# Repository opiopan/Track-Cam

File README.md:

trackCAM
---

trackCAM is a shield board for Raspberry Pi to realize 2 axis tracking camera controll capability and RC TX collaboration capability.

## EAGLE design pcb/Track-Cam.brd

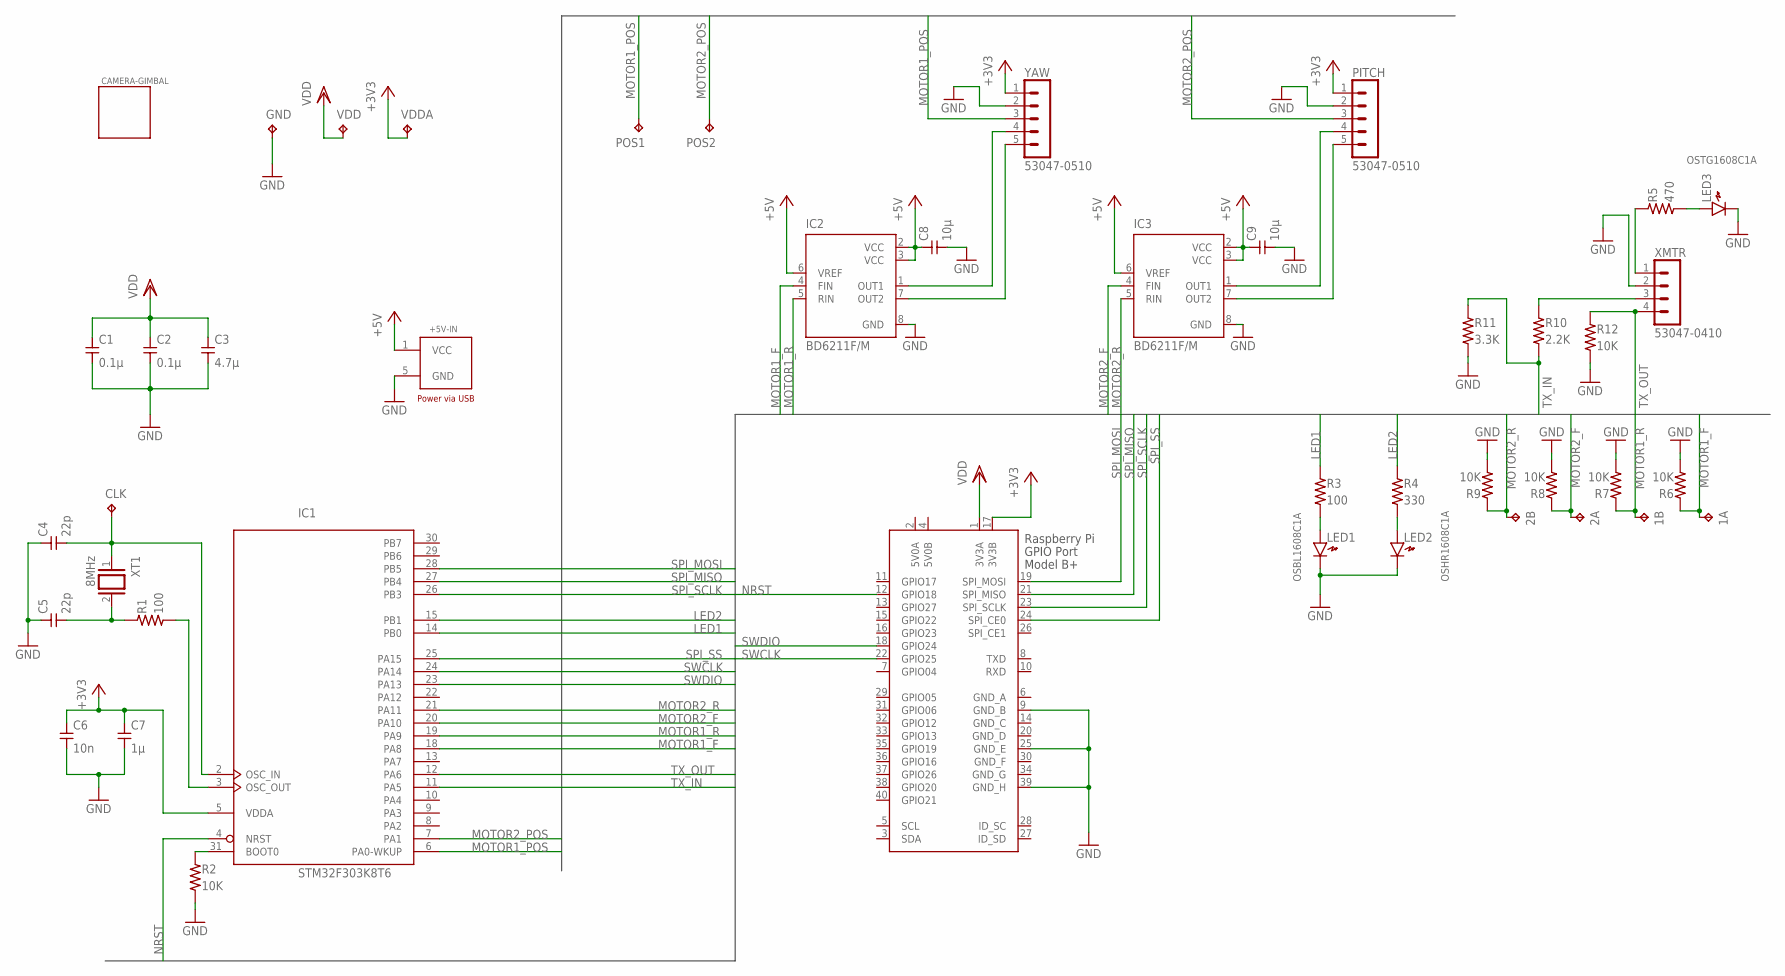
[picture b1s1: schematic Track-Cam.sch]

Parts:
1A, 1B, 2A, 2B: TPB1,27; B1,27
+5V-IN: MRUSB-2B-D14NI-S306/M; MICRO-USB-POWER/M
C1, C2: 0.1μ; SMD2012
C3: 4.7μ; SMD2012
C4, C5: 22p; SMD1608
C6: 10n; SMD2012
C7: 1μ; SMD2012
C8, C9: 10μ; SMD2012
CAMERA-GIMBAL: SG-90-CAMERA-MOUNT/NR; SG90-CAMERA-MOUNT-NR
CLK: TPB1,27; B1,27
GND: TPB1,27; B1,27
IC1: STM32F303K8T6; LQFP32-M
IC2, IC3: BD6211F/M; SOP8/M
LED1, LED2, LED3: LED1608
P1: RASPI_BOARD_B+#_HC; RASPI_BOARD_B+HAT_CF
PITCH: 53047-0510
POS1, POS2: TPB1,27; B1,27
R1, R3: 100; SMD2012
R2, R6, R7, R8, R9, R12: 10K; SMD2012
R4: 330; SMD2012
R5: 470; SMD2012
R10: 2.2K; SMD2012
R11: 3.3K; SMD2012
VDD: TPB1,27; B1,27
VDDA: TPB1,27; B1,27
XMTR: 53047-0410
XT1: 8MHz; QS
YAW: 53047-0510

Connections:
5V0A: P1.2 (5V0A)
5V0B: P1.4 (5V0B)
+3V3: C6.1, C7.1, IC1.5 (VDDA), P1.17 (3V3B), PITCH.1, VDDA.TP, YAW.1
+5V: +5V-IN.1 (VCC), C8.1, C9.1, IC2.2 (VCC), IC2.3 (VCC), IC2.6 (VREF), IC3.2 (VCC), IC3.3 (VCC), IC3.6 (VREF)
BOOT0: IC1.31 (BOOT0), R2.1
GND: +5V-IN.5 (GND), C1.2, C2.2, C3.2, C4.1, C5.1, C6.2, C7.2, C8.2, C9.2, GND.TP, IC1.16 (GND), IC1.32 (GND), IC2.8 (GND), IC3.8 (GND), LED1.K, LED2.K, LED3.K, P1.9 (GND_B), P1.25 (GND_E), P1.39 (GND_H), PITCH.2, R2.2, R6.2, R7.2, R8.2, R9.2, R11.2, R12.2, XMTR.2, YAW.2
GND_A: P1.6 (GND_A)
GND_C: P1.14 (GND_C)
GND_D: P1.20 (GND_D)
GND_F: P1.30 (GND_F)
GND_G: P1.34 (GND_G)
LED1: IC1.14 (PB0), R3.1
LED2: IC1.15 (PB1), R4.1
MOTOR1+: IC2.1 (OUT1), YAW.4
MOTOR1-: IC2.7 (OUT2), YAW.5
MOTOR1_F: 1A.TP, IC1.18 (PA8), IC2.4 (FIN), R6.1
MOTOR1_POS: IC1.6 (PA0-WKUP), POS1.TP, YAW.3
MOTOR1_R: 1B.TP, IC1.19 (PA9), IC2.5 (RIN), R7.1
MOTOR2+: IC3.1 (OUT1), PITCH.4
MOTOR2-: IC3.7 (OUT2), PITCH.5
MOTOR2_F: 2A.TP, IC1.20 (PA10), IC3.4 (FIN), R8.1
MOTOR2_POS: IC1.7 (PA1), PITCH.3, POS2.TP
MOTOR2_R: 2B.TP, IC1.21 (PA11), IC3.5 (RIN), R9.1
unnamed: C5.2, R1.1, XT1.2
unnamed: LED1.A, R3.2
unnamed: LED2.A, R4.2
unnamed: R5.1, XMTR.1
unnamed: LED3.A, R5.2
NRST: IC1.4 (NRST), P1.12 (GPIO18)
OSC_IN: C4.2, CLK.TP, IC1.2 (OSC_IN), XT1.1
OSC_OUT: IC1.3 (OSC_OUT), R1.2
SPI_MISO: IC1.27 (PB4), P1.21 (SPI_MISO)
SPI_MOSI: IC1.28 (PB5), P1.19 (SPI_MOSI)
SPI_SCLK: IC1.26 (PB3), P1.23 (SPI_SCLK)
SPI_SS: IC1.25 (PA15), P1.24 (SPI_CE0)
SWCLK: IC1.24 (PA14), P1.22 (GPIO25)
SWDIO: IC1.23 (PA13), P1.18 (GPIO24)
TX_IN: IC1.11 (PA5), R10.2, R11.1
TX_IN_5V: R10.1, XMTR.3
TX_OUT: IC1.12 (PA6), R12.1, XMTR.4
VDD: C1.1, C2.1, C3.1, IC1.1 (VDD), IC1.17 (VDD), P1.1 (3V3A), VDD.TP

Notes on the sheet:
OSBL1608C1A
OSHR1608C1A
OSTG1608C1A

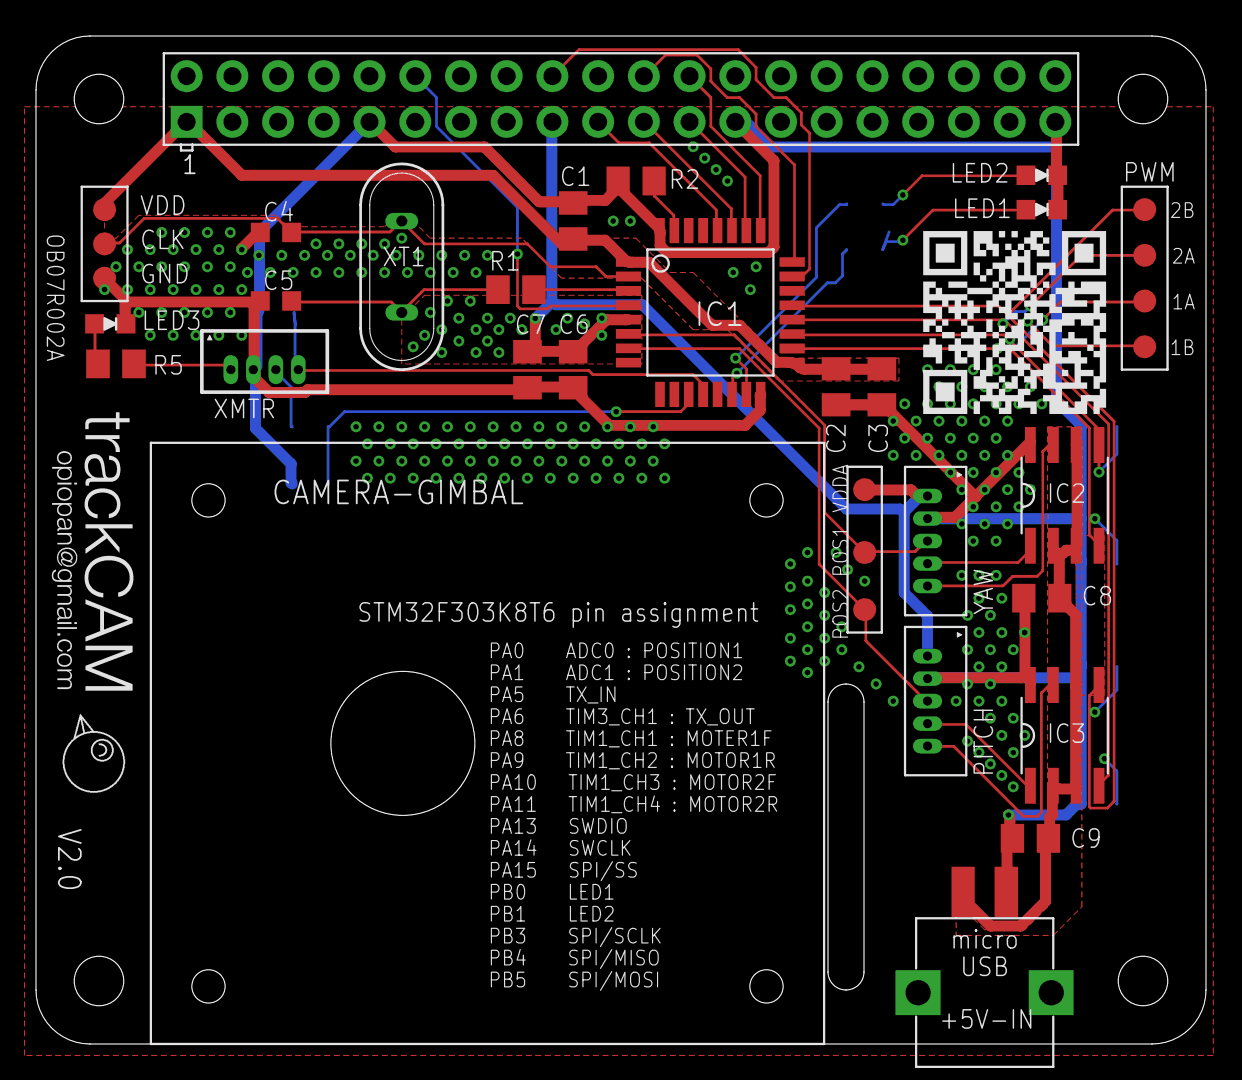
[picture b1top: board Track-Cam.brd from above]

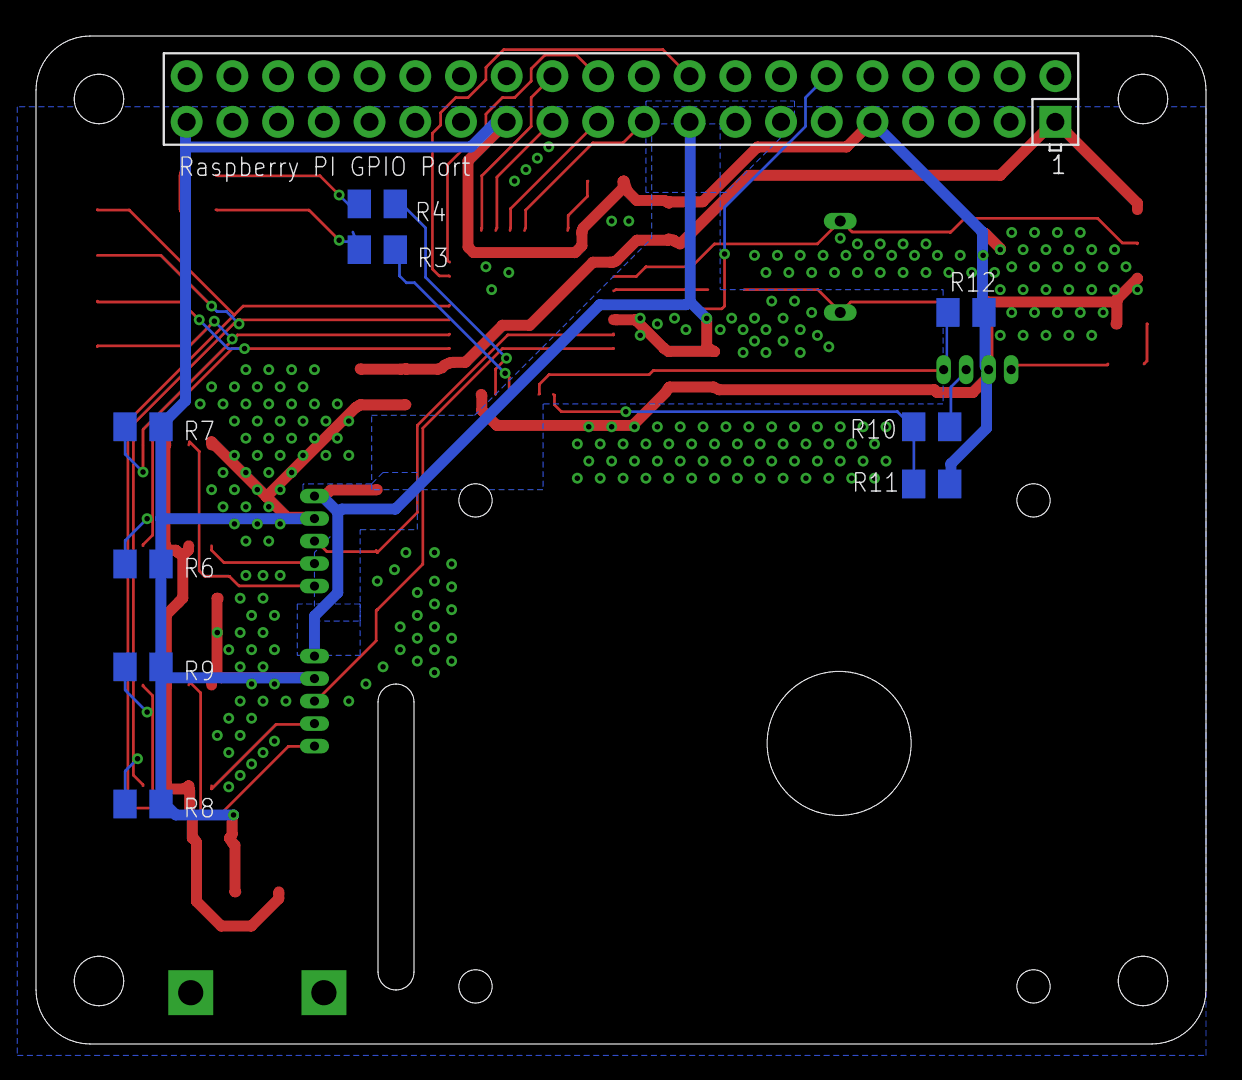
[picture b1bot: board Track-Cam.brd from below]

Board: 2 copper layers, 65.0 x 56.0 mm, 47 parts (9 on the bottom side), 34 nets.

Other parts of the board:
U$1: OPIOPAN-LOGO
U$2: TRACKCAM-LOGO
U$3: TRACKCAM-QRCODE

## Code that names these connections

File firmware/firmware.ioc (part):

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Mcu.Name=STM32F042K6Tx
Mcu.Package=LQFP32
Mcu.UserName=STM32F042K6Tx
PA0.Mode=IN0
PA0.Signal=ADC_IN0
PA1.Mode=IN1
PA1.Signal=ADC_IN1
PA10.Signal=S_TIM1_CH3
PA11.Signal=S_TIM1_CH4
PA13.Mode=Serial_Wire
PA13.Signal=SYS_SWDIO
PA14.Mode=Serial_Wire
PA14.Signal=SYS_SWCLK
PA5.Signal=GPIO_Input
PA6.Signal=GPIO_Output
PA8.Signal=S_TIM1_CH1
PA9.Signal=S_TIM1_CH2
PB0.Signal=GPIO_Output
PB1.Signal=GPIO_Output
PB3.Mode=Full_Duplex_Slave
PB3.Signal=SPI1_SCK
PB4.Mode=Full_Duplex_Slave
PB4.Signal=SPI1_MISO
PB5.Mode=Full_Duplex_Slave
PB5.Signal=SPI1_MOSI
PF0-OSC_IN.Mode=HSE-External-Oscillator
PF0-OSC_IN.Signal=RCC_OSC_IN
PF1-OSC_OUT.Mode=HSE-External-Oscillator
PF1-OSC_OUT.Signal=RCC_OSC_OUT
RCC.SYSCLKFreq_VALUE=48000000
RCC.SYSCLKSource=RCC_SYSCLKSOURCE_PLLCLK
board=firmware

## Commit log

2017-02-08 update .gitignore file
2017-02-09 enlarge pads
2017-02-11 fix issue of unconnected path
2017-02-11 add polygon net
2017-02-12 replaced components to confirm to actual gimbal size
2017-02-12 optimized grand path
2017-02-12 apply solid wiring
2017-02-13 improve silk design
2017-02-13 add via holes for noise immunity
2017-02-14 fix some bug
2017-02-16 optimize wiring
2017-02-17 fix some wiring bug
2017-02-17 fix 5v line bug
2017-03-01 fix BOM for 1st production
2017-03-09 add firmware template
2017-03-13 imprement basic host communication functions
2017-03-16 add LED capability
2017-03-19 impremented servo cotrol function
2017-03-20 add raspberry pi debug environment
2017-03-20 fix servo control issue
2017-03-26 implement PID feedback control
2017-04-02 improve PID controller
2017-04-07 improve PID controler
2017-04-14 change pcb design as connecting with Rasbery Pi by SPI
2017-04-14 improved pcb pattern
2017-04-18 modify firmware for V2.0 pcb
2017-04-23 add a project for STM32F3x
2017-04-23 fix a issue of SPI protcol
2017-04-23 arrange file placement
2017-04-24 improve host communication protcol
2017-04-25 add library and cli for Raspberry Pi
2017-04-25 improve interoperability
2017-04-25 fix a bug
2017-04-26 reformating c source
2017-04-26 determining servo position function was added to raspbery pi command
2017-04-26 renumbering command number
2017-04-26 add servo control feature to cli on Raspberry Pi
2017-04-26 fix TIM1 configuration bug
2017-04-29 change PID parameters
2017-04-30 add service on Raspberry Pi
2017-04-30 fix a issue of service on raspberry pi
2017-04-30 change startup sequence
2017-05-01 improve PID control logic
2017-05-02 change cover design
2017-05-19 add a function to retrieve servo position with time
2017-05-20 fix endian bug
2017-05-21 add position capturing feature
2017-05-21 improve error handler in firmware
2017-05-21 improve servo position capturing function
2017-05-27 change pcb cad version
2017-06-08 modify trackcam servo comannd with -c option to accept sub second value
2019-01-09 optimize pcb design to suport 3D model
